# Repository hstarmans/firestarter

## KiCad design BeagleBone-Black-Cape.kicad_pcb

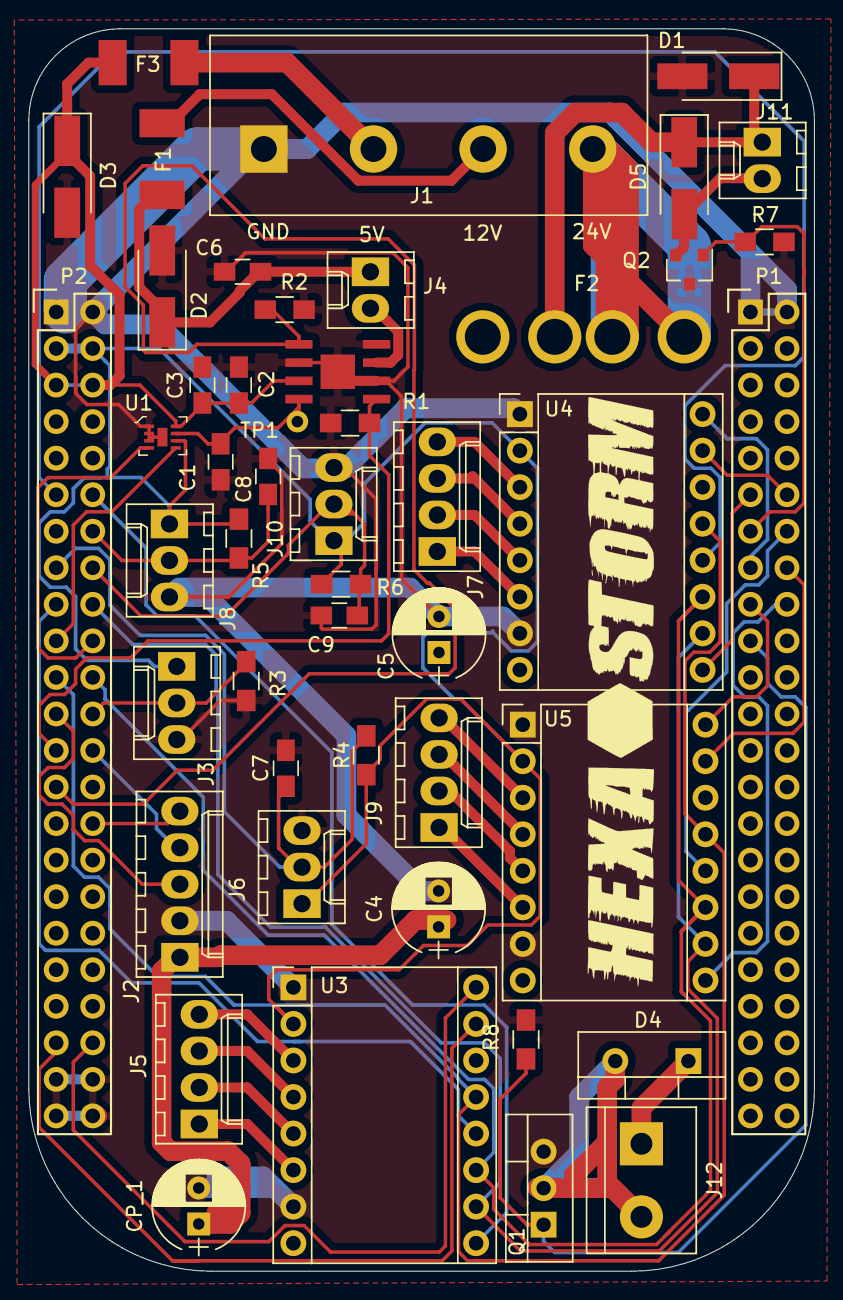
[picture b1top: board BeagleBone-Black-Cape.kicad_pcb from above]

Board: 2 copper layers, 54.6 x 86.4 mm, 49 parts (0 on the bottom side), 52 nets.

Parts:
C1: 47nF; C_0805_HandSoldering
C2, C6: 1uF; C_0805_HandSoldering
C3, C7, C8, C9: 0.1uF; C_0805_HandSoldering
C4, C5: 100uF; CP_Radial_D6.3mm_P2.50mm
CP_1: 100uF; CP_Radial_D6.3mm_P2.50mm
D1, D2, D3, D5: 50V_1A; D_SMA_Handsoldering
D4: STPS1545D; TO-220-2_Vertical
F1: 2A; littlefuse_448
F2: 30A; MCCQ-121
F3: 4A; littlefuse_448
G1: hexastorm
J1: MC000052
J2: MOLEX_2051; Molex_KK-6410-05_05x2.54mm_Straight
J3, J6, J8, J10: MOLEX_2031; Molex_KK-6410-03_03x2.54mm_Straight
J4, J11: MOLEX_2021; Molex_KK-6410-02_02x2.54mm_Straight
J5, J7, J9: MOLEX_2041; Molex_KK-6410-04_04x2.54mm_Straight
J12: EBV-02-D; TerminalBlock_bornier-2_P5.08mm
P1, P2: BeagleBone_Black_Header; Socket_BeagleBone_Black
Q1: IRLB8721PBF; TO-220-3_Vertical
Q2: IRFML8244; SOT-23
R1, R2, R4, R5, R6, R7, R8: 10K; R_0805_HandSoldering
R3: 340K; R_0805_HandSoldering
TP1: TestPoint; Measurement_Point_Round-TH_Small
U1: DIGIPOT_50K; TDFN-8-1EP
U2: U_IC-HKB; ICHKB
U3: X_STEPPER; TMC2130
U4: Y_STEPPER; TMC2130
U5: Z_STEPPER; TMC2130

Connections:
+3V3: J3.1, J6.1, J8.1, J10.1, P2.3, P2.4, R4.1, R5.1, R6.1, U1.6, U3.10, U4.10, U5.10
+5V: C2.2, C3.2, D3.1, F3.1, P2.5, P2.6, U1.8, U2.7
+12V: C6.1, D2.1, F1.1, J4.1
+24V: C4.1, C5.1, CP_1.1, D1.1, D4.1, D5.1, F2.3, F2.4, J2.1, J11.1, J12.1, U3.16, U4.16, U5.16
FAN_PWM: P1.13, Q2.1, R7.2
GND: C1.1, C2.1, C3.1, C4.2, C5.2, C6.2, C7.2, C8.2, C9.2, CP_1.2, D1.2, D2.2, D3.2, J1.1, J2.2, J3.3, J6.3, J8.3, J10.3, P1.1, P1.2, P2.1, P2.2, P2.43, P2.44, P2.45, P2.46, Q1.3, Q2.3, R1.2, R2.1, R3.1, R7.1, R8.1, U1.1, U1.2, U1.3, U1.9, U2.2, U2.4, U2.6, U2.9, U3.9, U3.15, U4.9, U4.15, U5.9, U5.15
IC_HB_PWM1: P2.25, R1.1, U2.1
IC_HB_PWM2: P2.27, R2.2, U2.5
LDK: J4.2, U2.3
unnamed: D4.2, J12.2, Q1.2
unnamed: D5.2, J11.2, Q2.2
unnamed: F1.2, J1.3
unnamed: F2.1, F2.2, J1.4
unnamed: F3.2, J1.2
PH_DIODE: J3.2, P2.24, R3.2
POLY_EN: J2.3, P2.23
POLY_PWM: J2.5, P2.30
POLY_READY: J2.4, P2.26
POT_SCL: P2.19, U1.5
POT_SDA: P2.20, U1.4
POT_W: C1.2, TP1.1, U1.7, U2.8
SPI0_CSX: P2.17, U3.4
SPINDLE_PWM: P1.19, Q1.1, R8.2
SPIO_CSY: P2.11, U4.4
SPIO_CSZ: P1.14, U5.4
SPIO_DI: P2.18, U3.2, U4.2, U5.2
SPIO_DO: P2.21, U3.5, U4.5, U5.5
SPIO_SCL: P2.22, U3.3, U4.3, U5.3
X_1A: J5.3, U3.12
X_1B: J5.4, U3.11
X_2A: J5.2, U3.13
X_2B: J5.1, U3.14
X_DIR: P2.42, U3.8
X_ENABLE: P2.12, U3.1
X_PO: C7.1, J6.2, P2.15, R4.2
X_STEP: P2.41, U3.7
Y_1A: J7.3, U4.12
Y_1B: J7.4, U4.11
Y_2A: J7.2, U4.13
Y_2B: J7.1, U4.14
Y_DIR: P1.15, U4.8
Y_ENABLE: P1.11, U4.1
Y_PO: C8.1, J8.2, P2.14, R5.2
Y_STEP: P1.12, U4.7
Z_1A: J9.3, U5.12
Z_1B: J9.4, U5.11
Z_2A: J9.2, U5.13
Z_2B: J9.1, U5.14
Z_DIR: P1.17, U5.8
Z_ENABLE: P1.18, U5.1
Z_PO: C9.1, J10.2, P2.16, R6.2
Z_STEP: P1.16, U5.7

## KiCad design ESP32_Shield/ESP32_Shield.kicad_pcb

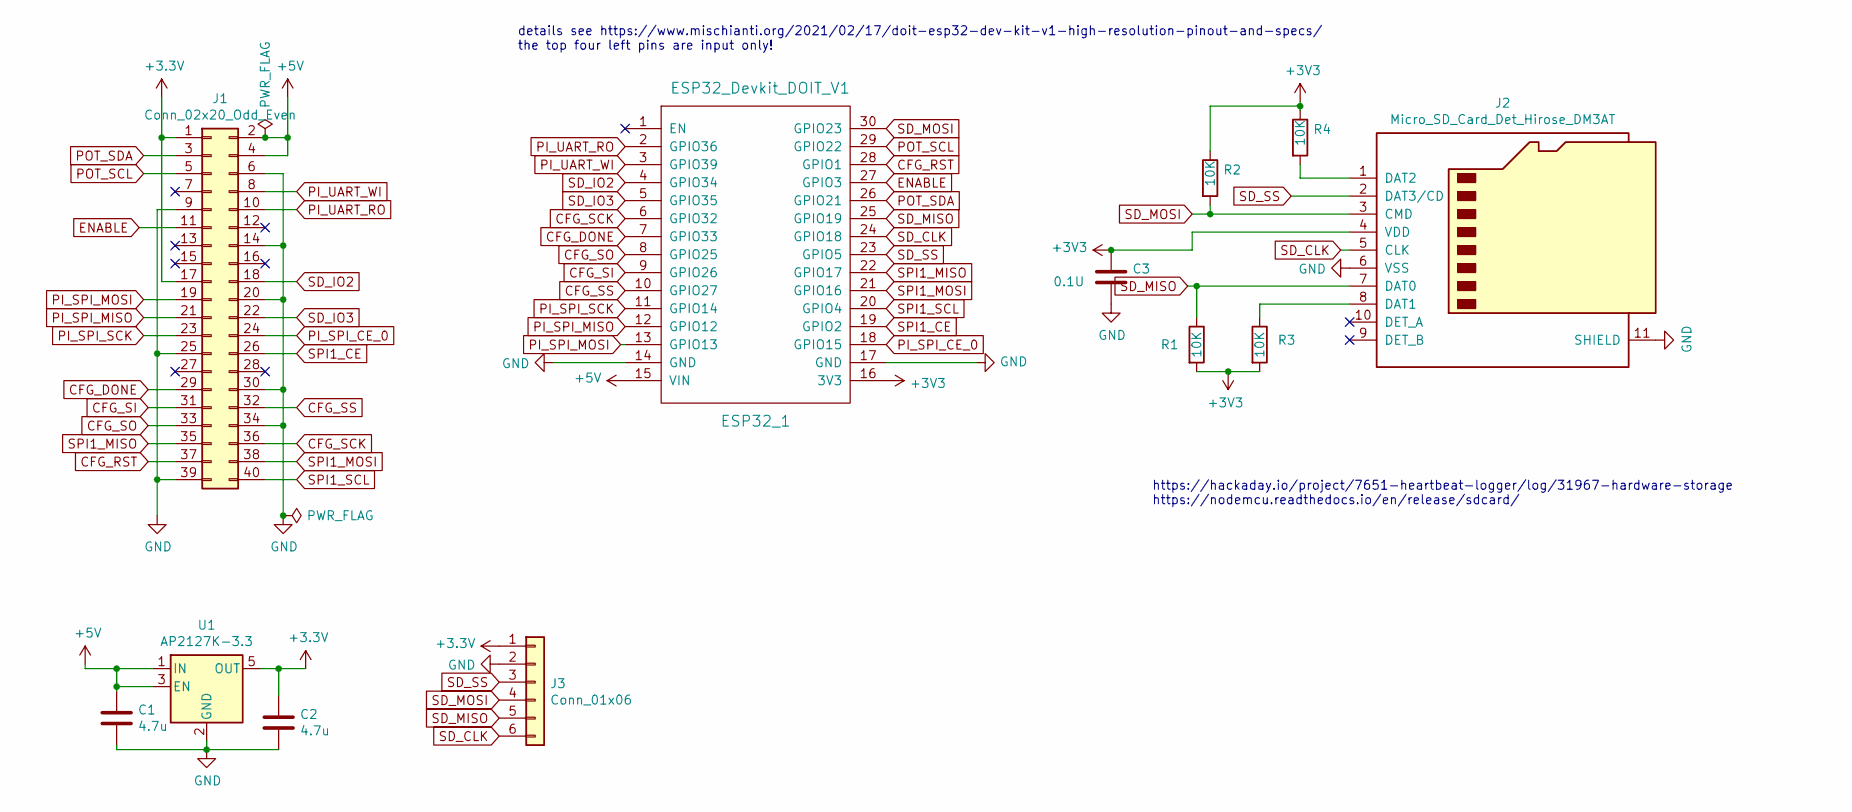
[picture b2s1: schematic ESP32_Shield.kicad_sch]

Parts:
C1, C2: 4.7u; C_0805_2012Metric_Pad1.18x1.45mm_HandSolder
C3: 0.1U; C_0805_2012Metric_Pad1.18x1.45mm_HandSolder
ESP32_1: ESP32_Devkit_DOIT_V1
J1: Conn_02x20_Odd_Even; PinHeader_2x20_P2.54mm_Vertical
J2: Micro_SD_Card_Det_Hirose_DM3AT; microSD_HC_Hirose_DM3AT-SF-PEJM5
J3: Conn_01x06; PinHeader_1x06_P2.54mm_Vertical
R1, R2, R3, R4: 10K; R_0805_2012Metric
U1: AP2127K-3.3; SOT-23-5

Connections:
+5V: C1.1, ESP32_1.15 (VIN), J1.2, J1.4, U1.1 (IN), U1.3 (EN)
CFG_DONE: ESP32_1.7 (GPIO33), J1.29
CFG_RST: ESP32_1.28 (GPIO1), J1.37
CFG_SCK: ESP32_1.6 (GPIO32), J1.36
CFG_SI: ESP32_1.9 (GPIO26), J1.31
CFG_SO: ESP32_1.8 (GPIO25), J1.33
CFG_SS: ESP32_1.10 (GPIO27), J1.32
ENABLE: ESP32_1.27 (GPIO3), J1.11
GND: C1.2, C2.2, C3.2, ESP32_1.14 (GND), ESP32_1.17 (GND), J1.6, J1.9, J1.14, J1.20, J1.25, J1.30, J1.34, J1.39, J2.6 (VSS), J2.11 (SHIELD), J3.2, U1.2 (GND)
unnamed: J2.1 (DAT2), R4.2
unnamed: J2.8 (DAT1), R3.1
PI_SPI_CE_0: ESP32_1.18 (GPIO15), J1.24
PI_SPI_MISO: ESP32_1.12 (GPIO12), J1.21
PI_SPI_MOSI: ESP32_1.13 (GPIO13), J1.19
PI_SPI_SCK: ESP32_1.11 (GPIO14), J1.23
PI_UART_RO: ESP32_1.2 (GPIO36), J1.10
PI_UART_WI: ESP32_1.3 (GPIO39), J1.8
POT_SCL: ESP32_1.29 (GPIO22), J1.5
POT_SDA: ESP32_1.26 (GPIO21), J1.3
SD_CLK: ESP32_1.24 (GPIO18), J2.5 (CLK), J3.6
SD_IO2: ESP32_1.4 (GPIO34), J1.18
SD_IO3: ESP32_1.5 (GPIO35), J1.22
SD_MISO: ESP32_1.25 (GPIO19), J2.7 (DAT0), J3.5, R1.1
SD_MOSI: ESP32_1.30 (GPIO23), J2.3 (CMD), J3.4, R2.2
SD_SS: ESP32_1.23 (GPIO5), J2.2 (DAT3/CD), J3.3
SPI1_CE: ESP32_1.19 (GPIO2), J1.26
SPI1_MISO: ESP32_1.22 (GPIO17), J1.35
SPI1_MOSI: ESP32_1.21 (GPIO16), J1.38
SPI1_SCL: ESP32_1.20 (GPIO4), J1.40

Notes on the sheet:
details see https://www.mischianti.org/2021/02/17/doit-esp32-dev-kit-v1-high-resolution-pinout-and-specs/ the top four left pins are input only!
https://hackaday.io/project/7651-heartbeat-logger/log/31967-hardware-storage https://nodemcu.readthedocs.io/en/release/sdcard/

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
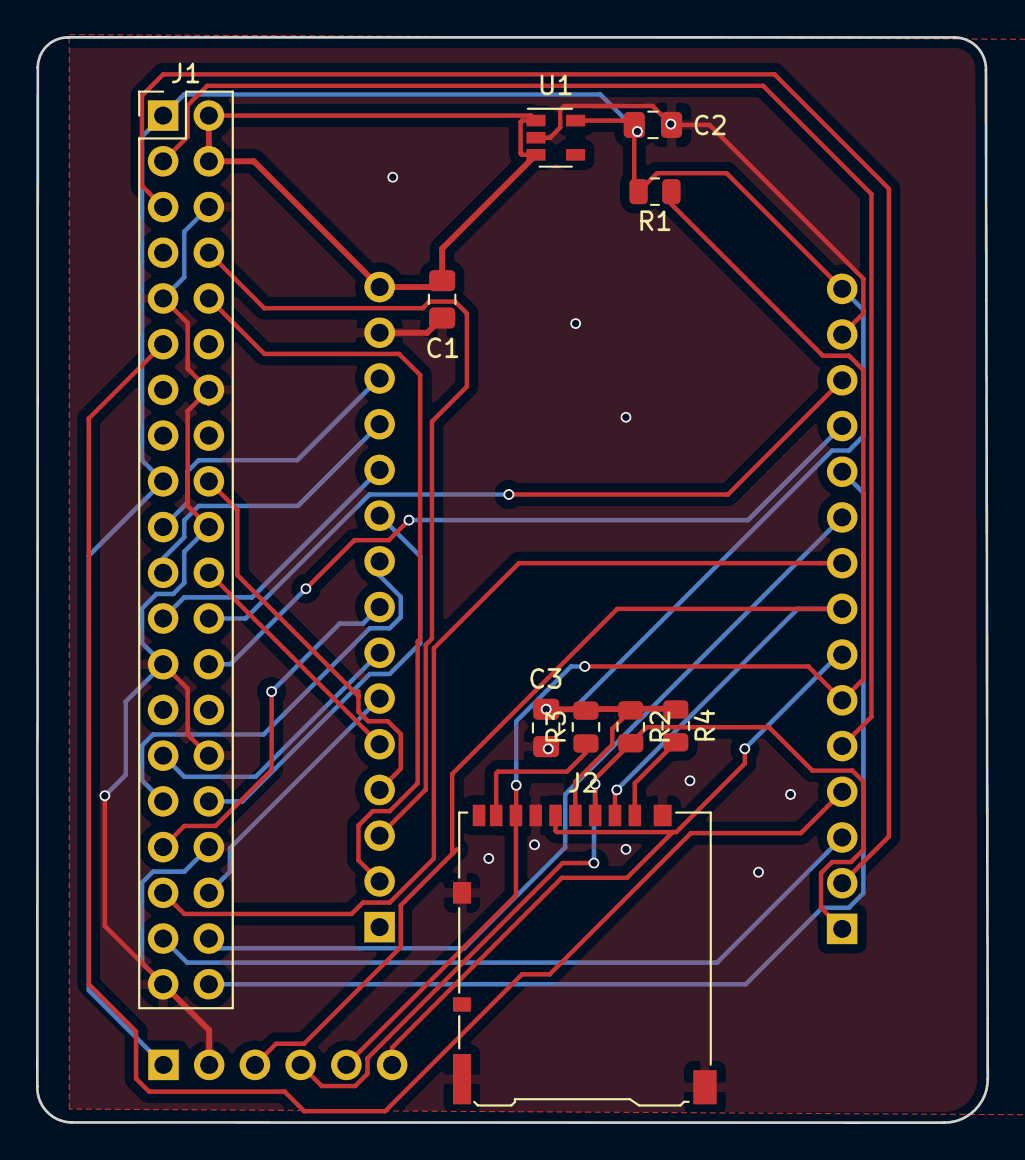
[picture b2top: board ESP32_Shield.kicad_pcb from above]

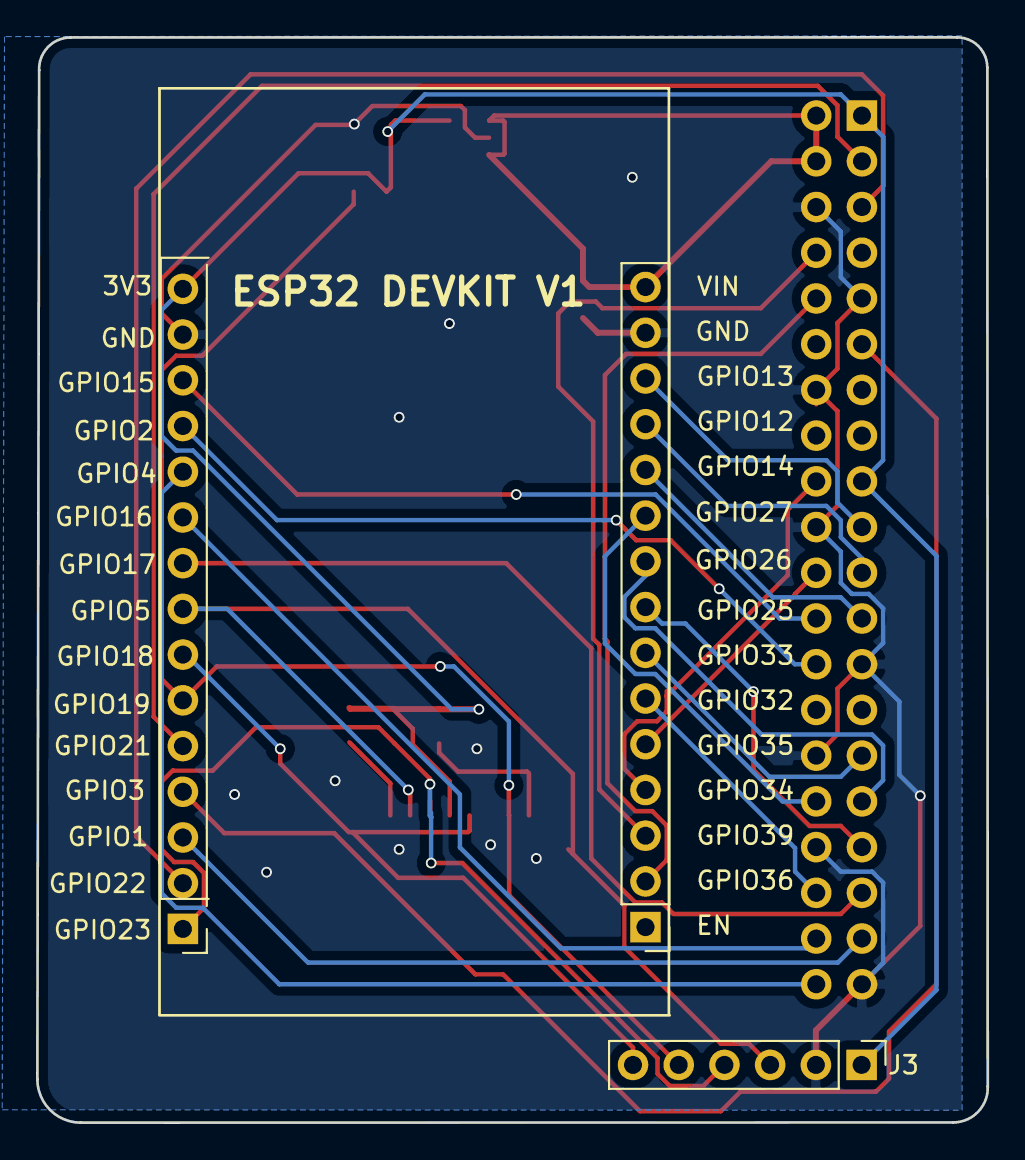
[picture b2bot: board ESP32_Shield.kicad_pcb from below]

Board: 2 copper layers, 52.8 x 60.3 mm, 12 parts (2 on the bottom side), 30 nets.

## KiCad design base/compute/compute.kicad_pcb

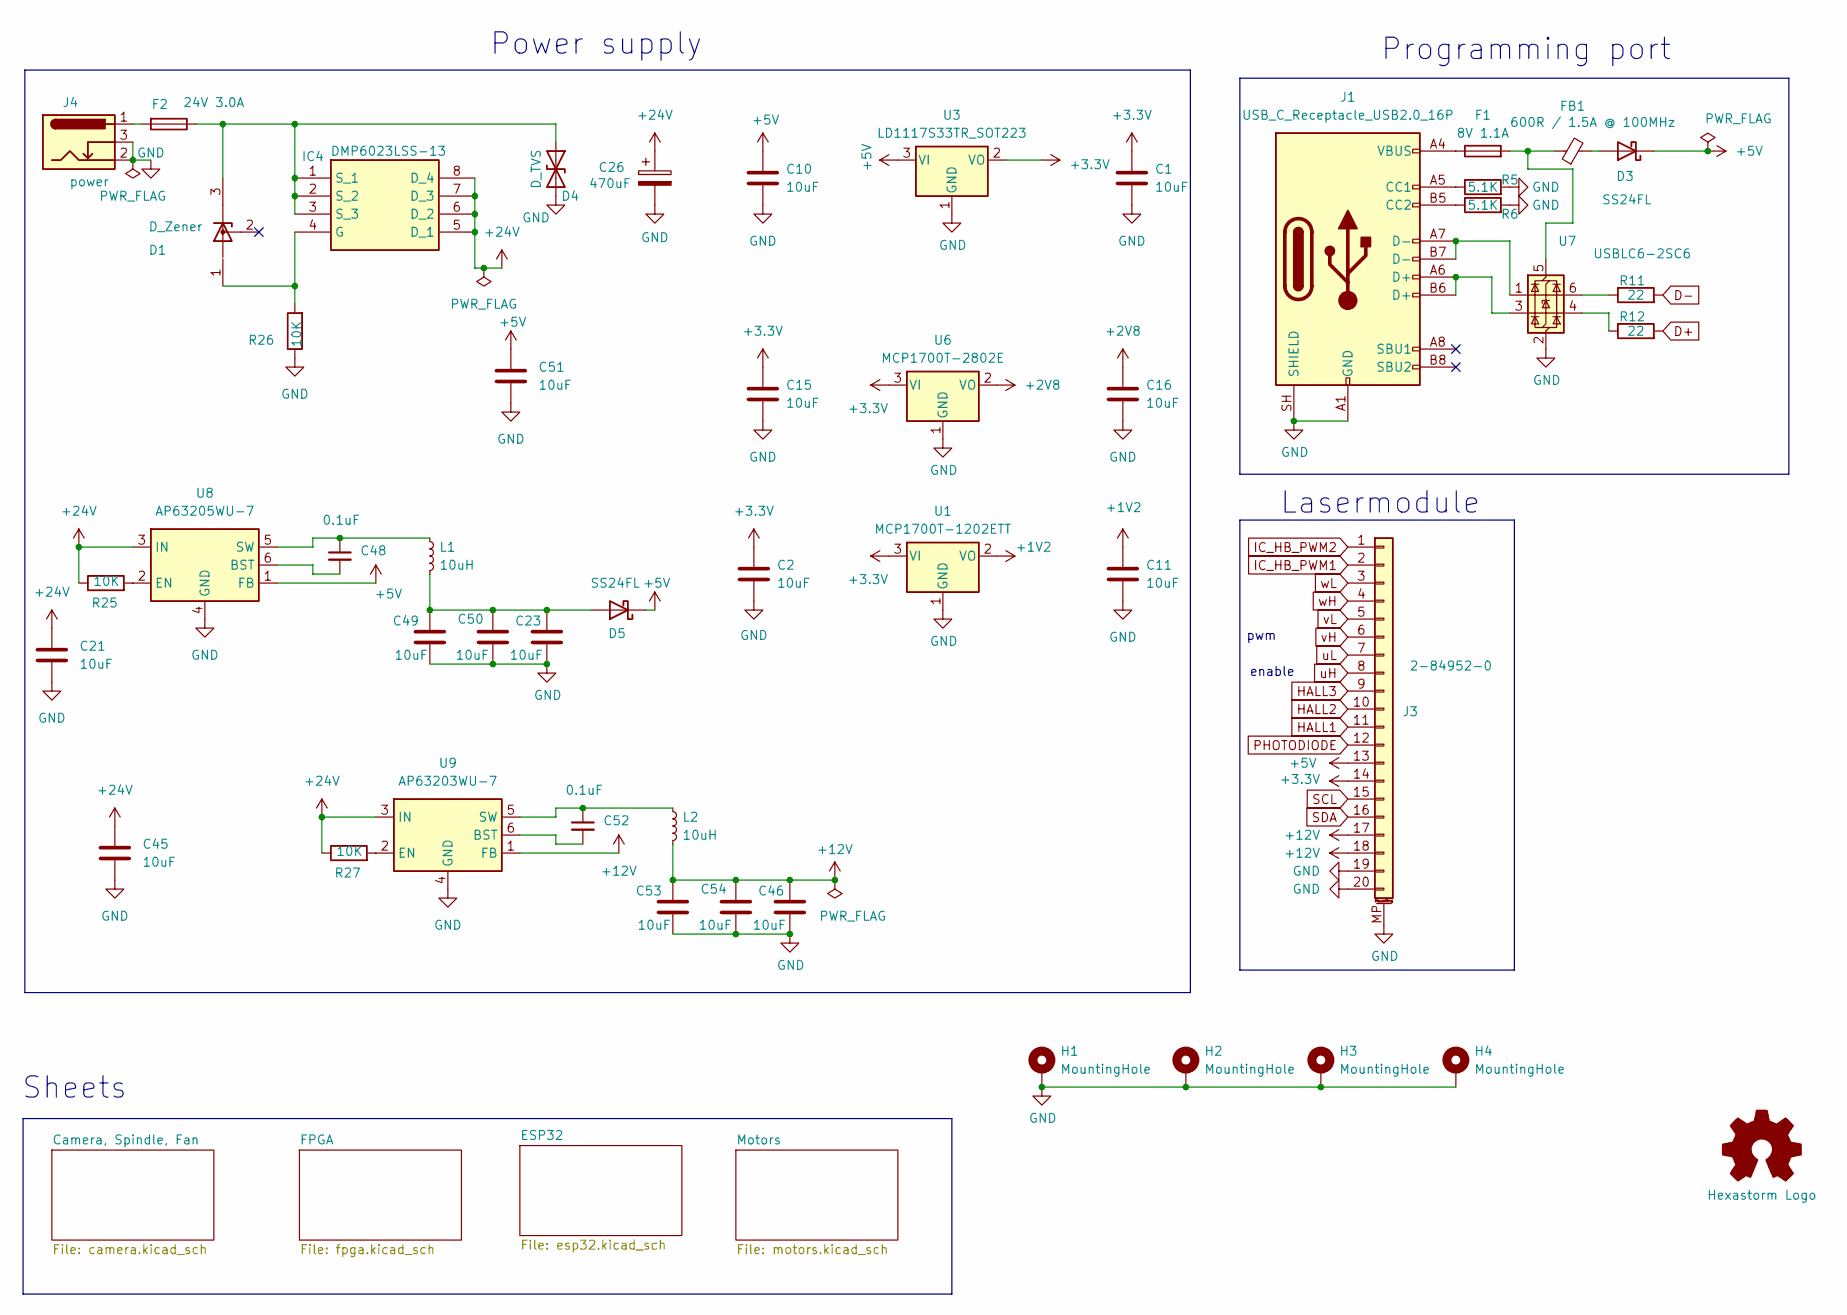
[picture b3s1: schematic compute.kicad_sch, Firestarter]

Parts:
C1, C2, C10, C11, C15, C16, C49, C50, C53, C54: 10uF; C_0805_2012Metric_Pad1.18x1.45mm_HandSolder; mouser# 81-GRM21BR61H106KE3L; farnell# 3790440
C21, C23, C45, C46, C51: 10uF; C_0805_2012Metric_Pad1.18x1.45mm_HandSolder; mouser# 81-GRM21BR61H106KE3L
C26: 470uF; CP_Elec_10x10.5; mouser# 667-EEE-FK1V471SP; farnell# 2507737
C48, C52: 0.1uF; C_0805_2012Metric_Pad1.18x1.45mm_HandSolder; mouser# 80-C0805C104J5R
D1: D_Zener; SOT-23; mouser# 2675184
D3, D5: SS24FL; D_SMA; mouser# 512-SS24FL; farnell# 2822566
D4: D_TVS; D_SMB; mouser# 652-SMBJ13CA; farnell# 2765106
F1: 8V 1.1A; Fuse_1206_3216Metric; mouser# 576-1206L110THYR; farnell# 2383294
F2: 24V 3.0A; Fuse_2920_7451Metric; mouser# 652-MF-LSMF300/24X-2
FB1: 600R / 1.5A @ 100MHz; L_0805_2012Metric; mouser# 81-BLM21PG601SN1D
G1: hexastorm
H1, H2, H3, H4: MountingHole; MountingHole_2.2mm_M2_Pad_Via; mouser# 710-970050244
IC4: DMP6023LSS-13; SOIC-8_3.9x4.9mm_P1.27mm; Manufacturer_Part_Number DMP6023LSS-13; Mouser Part Number 621-DMP6023LSS-13
J1: USB_C_Receptacle_USB2.0_16P; USB_C_Receptacle_GCT_USB4105-xx-A_16P_TopMnt_Horizontal; mouser# 640-USB4105-GF-A
J3: 2-84952-0; mouser# 571-2-84952-0
J4: power; BarrelJack_CUI_PJ-036AH-SMT_Horizontal; mouser# 490-PJ-036AH-SMT-TR
L1, L2: 10uH; L_Bourns_SRP5030T; mouser# 652-SRP5030T-100M
R5, R6: 5.1K; R_0805_2012Metric; mouser# 71-CRCW0805-5.1K-E3; farnell# 1469937
R11, R12: 22; R_0805_2012Metric; mouser# 71-CRCW0805-22-E3; farnell# 1652962
R25, R26, R27: 10K; R_0805_2012Metric; mouser# 71-CRCW080510K0JNEAC; farnell# 2826162
U1: MCP1700T-1202ETT; SOT-23; mouser# 579-MCP1700T1202E/TT
U3: LD1117S33TR_SOT223; SOT-23; mouser# 511-LD1117S33C; farnell# 1467779
U6: MCP1700T-2802E; SOT-23; mouser# 579-MCP1700T-2802ETT
U7: USBLC6-2SC6; SOT-23-6; mouser# 511-USBLC6-2SC6; farnell# 1269406
U8: AP63205WU-7; TSOT-23-6; mouser# 621-AP63205WU-7; farnell# 3518308
U9: AP63203WU-7; TSOT-23-6; mouser# 621-AP63203WU-7; farnell# 3518307

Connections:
+1V2: C11.1, U1.2 (VO); also elsewhere on the board
+2V8: C16.1, U6.2 (VO); also elsewhere on the board
+3.3V: C1.1, C2.1, C15.1, J3.14, U1.3 (VI), U3.2 (VO), U6.3 (VI); also elsewhere on the board
+5V: C10.1, C51.1, D3.1 (K), D5.1 (K), J3.13, U3.3 (VI), U8.1 (FB)
+12V: C46.1, C53.1, C54.1, J3.17, J3.18, L2.2, U9.1 (FB); also elsewhere on the board
+24V: C21.1, C26.1, C45.1, IC4.5 (D_1), IC4.6 (D_2), IC4.7 (D_3), IC4.8 (D_4), R25.1, R27.1, U8.3 (IN), U9.3 (IN); also elsewhere on the board
D+: R12.2; also elsewhere on the board
D-: R11.2; also elsewhere on the board
GND: C1.2, C2.2, C10.2, C11.2, C15.2, C16.2, C21.2, C23.2, C26.2, C45.2, C46.2, C49.2, C50.2, C51.2, C53.2, C54.2, D4.2 (A2), H1.1 (1_1), H2.1 (1_1), H3.1 (1_1), H4.1 (1_1), J1.A1 (GND), J1.A12 (GND), J1.B1 (GND), J1.B12 (GND), J1.SH (SHIELD), J3.19, J3.20, J3.MP (MountPin), J4.2, J4.3, R5.2, R6.2, R26.1, U1.1 (GND), U3.1 (GND), U6.1 (GND), U7.2 (GND), U8.4 (GND), U9.4 (GND); also elsewhere on the board
HALL1: J3.11; also elsewhere on the board
HALL2: J3.10; also elsewhere on the board
HALL3: J3.9; also elsewhere on the board
IC_HB_PWM1: J3.2; also elsewhere on the board
IC_HB_PWM2: J3.1; also elsewhere on the board
unnamed: D3.2 (A), FB1.2
unnamed: D1.3 (K), D4.1 (A1), F2.1, IC4.1 (S_1), IC4.2 (S_2), IC4.3 (S_3)
unnamed: C23.1, C49.1, C50.1, D5.2 (A), L1.2
unnamed: F1.1, J1.A4 (VBUS), J1.A9 (VBUS), J1.B4 (VBUS), J1.B9 (VBUS)
unnamed: F2.2, J4.1
unnamed: D1.1 (K), IC4.4 (G), R26.2
unnamed: J1.A5 (CC1), R5.1
unnamed: J1.B5 (CC2), R6.1
unnamed: J1.A6 (D+), J1.B6 (D+), U7.3 (I/O2)
unnamed: J1.A7 (D-), J1.B7 (D-), U7.1 (I/O1)
unnamed: R11.1, U7.6 (I/O1)
unnamed: R12.1, U7.4 (I/O2)
unnamed: F1.2, FB1.1, U7.5 (VBUS)
unnamed: C48.2, U8.6 (BST)
unnamed: R25.2, U8.2 (EN)
unnamed: C48.1, L1.1, U8.5 (SW)
unnamed: C52.2, U9.6 (BST)
unnamed: R27.2, U9.2 (EN)
unnamed: C52.1, L2.1, U9.5 (SW)
PHOTODIODE: J3.12; also elsewhere on the board
SCL: J3.15; also elsewhere on the board
SDA: J3.16; also elsewhere on the board
uH: J3.8; also elsewhere on the board
uL: J3.7; also elsewhere on the board
vH: J3.6; also elsewhere on the board
vL: J3.5; also elsewhere on the board
wH: J3.4; also elsewhere on the board
wL: J3.3; also elsewhere on the board

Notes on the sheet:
pwm
Programming port
Sheets
Power supply
enable
Lasermodule

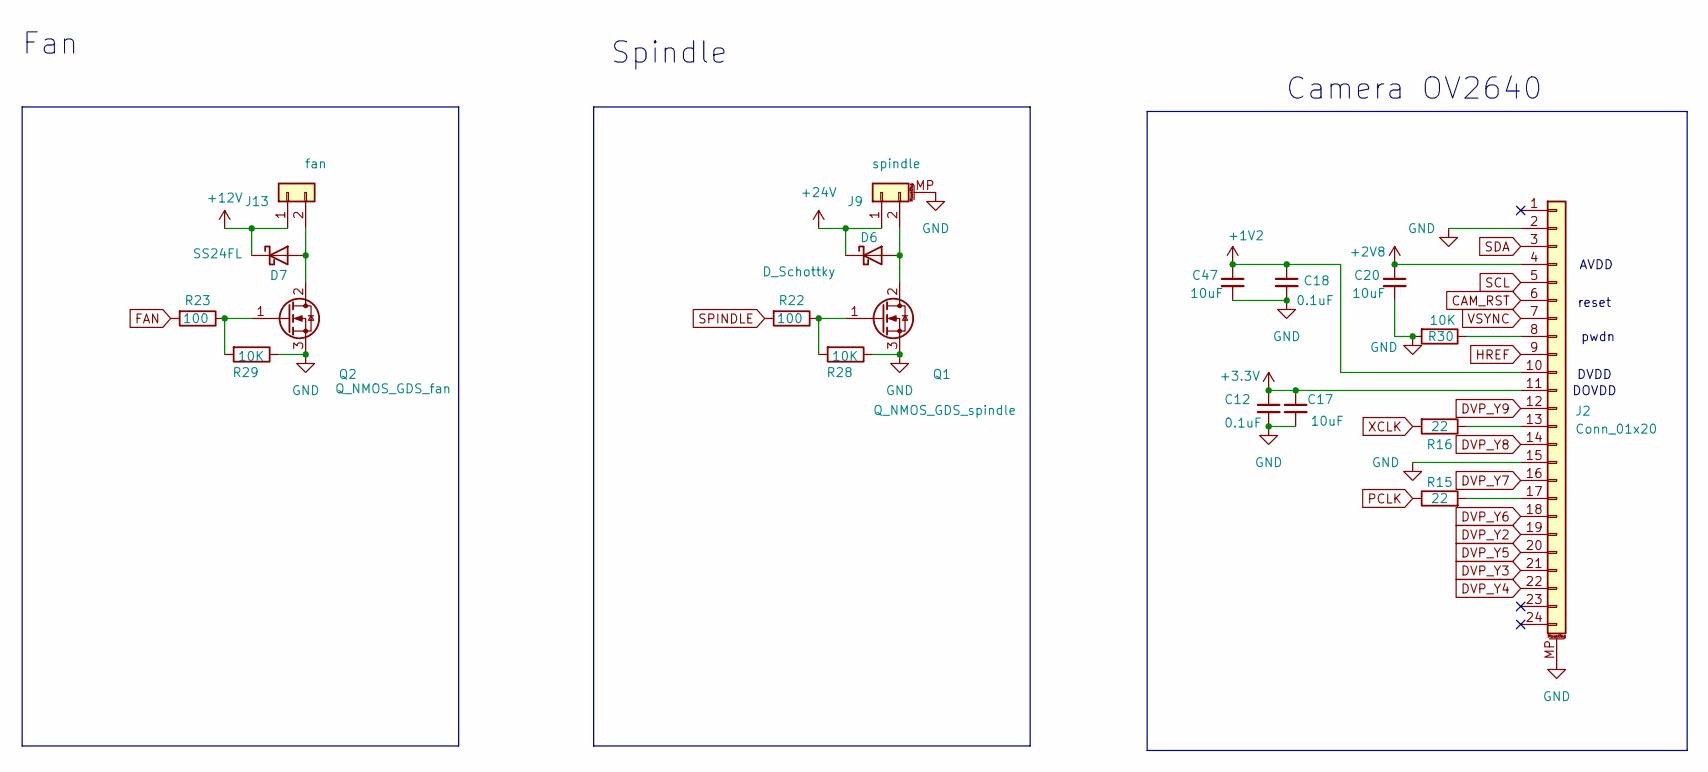
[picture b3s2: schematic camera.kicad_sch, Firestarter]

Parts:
C12, C18: 0.1uF; C_0805_2012Metric_Pad1.18x1.45mm_HandSolder; mouser# 80-C0805C104J5R
C17, C20, C47: 10uF; C_0805_2012Metric_Pad1.18x1.45mm_HandSolder; mouser# 81-GRM21BR61H106KE3L; farnell# 3790440
D6: D_Schottky; D_SMA; mouser# 750-SS56-HF
D7: SS24FL; D_SMA; mouser# 512-SS24FL; farnell# 2822566
J2: Conn_01x20; Hirose_FH12-24S-0.5SH_1x24-1MP_P0.50mm_Horizontal; mouser# 798-FH12-24S-0.5SH55; farnell# 1324552
J9: spindle; 21548291; mouser# 571-2154829-1
J13: fan; TSM-102-01-L-SV; mouser# 200-TSM10201TSV
Q1: Q_NMOS_GDS_spindle; TO-252-2; mouser# 511-STD120N4LF6
Q2: Q_NMOS_GDS_fan; SOT-23; mouser# 512-2N7002
R15, R16: 22; R_0805_2012Metric; mouser# 71-CRCW0805-22-E3; farnell# 1652962
R22, R23: 100; R_0805_2012Metric_Pad1.20x1.40mm_HandSolder; mouser# 71-CRCW0805-100
R28, R29, R30: 10K; R_0805_2012Metric; mouser# 71-CRCW080510K0JNEAC; farnell# 2826162

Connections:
+1V2: C18.1, C47.1, J2.10; also elsewhere on the board
+2V8: C20.1, J2.4; also elsewhere on the board
+3.3V: C12.1, C17.1, J2.11; also elsewhere on the board
+12V: D7.1 (K), J13.1; also elsewhere on the board
+24V: D6.1 (K), J9.1; also elsewhere on the board
CAM_RST: J2.6; also elsewhere on the board
DVP_Y2: J2.19; also elsewhere on the board
DVP_Y3: J2.21; also elsewhere on the board
DVP_Y4: J2.22; also elsewhere on the board
DVP_Y5: J2.20; also elsewhere on the board
DVP_Y6: J2.18; also elsewhere on the board
DVP_Y7: J2.16; also elsewhere on the board
DVP_Y8: J2.14; also elsewhere on the board
DVP_Y9: J2.12; also elsewhere on the board
FAN: R23.2; also elsewhere on the board
GND: C12.2, C17.2, C18.2, C20.2, C47.2, J2.2, J2.15, J2.MP (MountPin), J9.MP (MountPin), Q1.3 (S), Q2.3 (S), R28.1, R29.1, R30.2; also elsewhere on the board
HREF: J2.9; also elsewhere on the board
unnamed: D6.2 (A), J9.2, Q1.2 (D)
unnamed: D7.2 (A), J13.2, Q2.2 (D)
unnamed: J2.8, R30.1
unnamed: J2.13, R16.1
unnamed: J2.17, R15.2
unnamed: Q1.1 (G), R22.1, R28.2
unnamed: Q2.1 (G), R23.1, R29.2
PCLK: R15.1; also elsewhere on the board
SCL: J2.5; also elsewhere on the board
SDA: J2.3; also elsewhere on the board
SPINDLE: R22.2; also elsewhere on the board
VSYNC: J2.7; also elsewhere on the board
XCLK: R16.2; also elsewhere on the board

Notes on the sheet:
DOVDD
DVDD
Spindle
pwdn
reset
Fan
Camera OV2640
AVDD

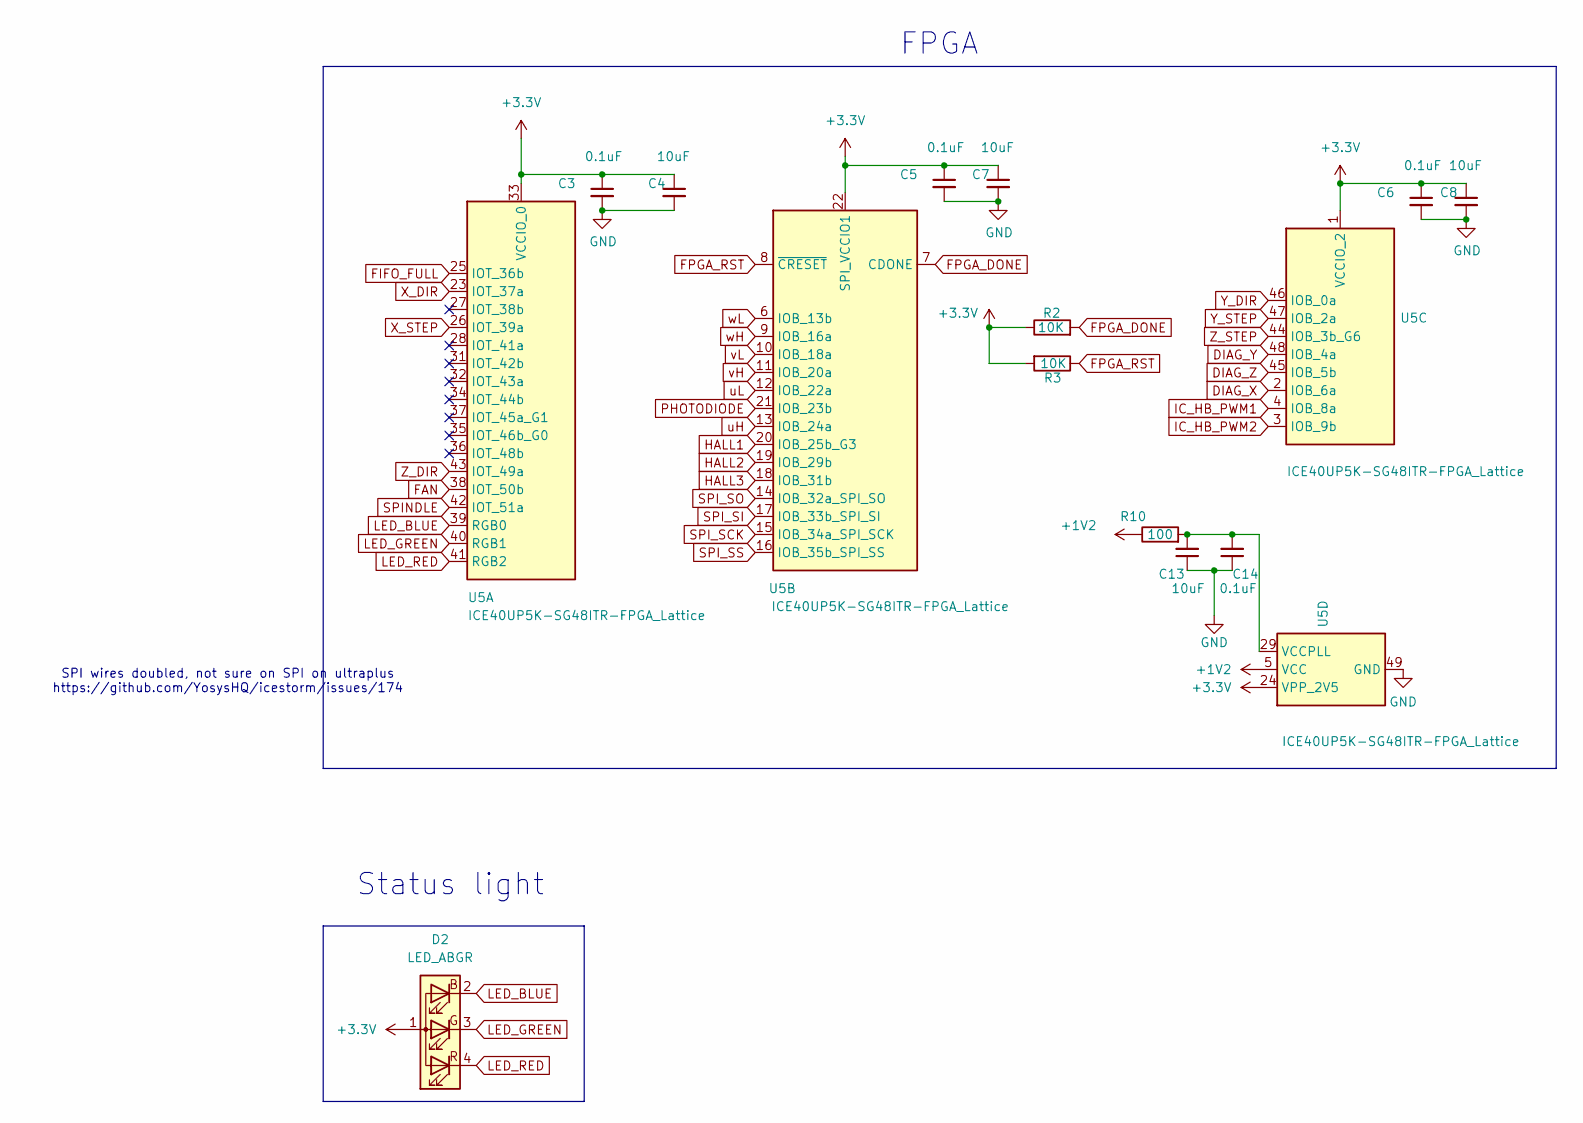
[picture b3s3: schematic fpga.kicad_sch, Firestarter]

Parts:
C3, C5, C6, C14: 0.1uF; C_0805_2012Metric_Pad1.18x1.45mm_HandSolder; mouser# 80-C0805C104J5R
C4, C7, C8, C13: 10uF; C_0805_2012Metric_Pad1.18x1.45mm_HandSolder; mouser# 81-GRM21BR61H106KE3L; farnell# 3790440
D2: LED_ABGR; LED_Cree-PLCC4_2x2mm_CW; mouser# 941-CLMVCFKACL1D1L71; farnell# 3625420
R2, R3: 10K; R_0805_2012Metric; mouser# 71-CRCW080510K0JNEAC; farnell# 2826162
R10: 100; R_0805_2012Metric_Pad1.20x1.40mm_HandSolder; mouser# 71-CRCW0805-100
U5: ICE40UP5K-SG48ITR-FPGA_Lattice; QFN-48-1EP_7x7mm_P0.5mm_EP5.6x5.6mm; mouser# 842-ICE40UP5K-SG48I

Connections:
+1V2: R10.1, U5.5 (VCC), U5.30 (VCC); also elsewhere on the board
+3.3V: C3.1, C4.1, C5.1, C6.1, C7.1, C8.1, D2.1 (A), R2.1, R3.2, U5.1 (VCCIO_2), U5.22 (SPI_VCCIO1), U5.24 (VPP_2V5), U5.33 (VCCIO_0); also elsewhere on the board
DIAG_X: U5.2 (IOB_6a); also elsewhere on the board
DIAG_Y: U5.48 (IOB_4a); also elsewhere on the board
DIAG_Z: U5.45 (IOB_5b); also elsewhere on the board
FAN: U5.38 (IOT_50b); also elsewhere on the board
FIFO_FULL: U5.25 (IOT_36b); also elsewhere on the board
FPGA_DONE: R2.2, U5.7 (CDONE); also elsewhere on the board
FPGA_RST: R3.1, U5.8 (~CRESET); also elsewhere on the board
GND: C3.2, C4.2, C5.2, C6.2, C7.2, C8.2, C13.1, C14.1, U5.49 (GND); also elsewhere on the board
HALL1: U5.20 (IOB_25b_G3); also elsewhere on the board
HALL2: U5.19 (IOB_29b); also elsewhere on the board
HALL3: U5.18 (IOB_31b); also elsewhere on the board
IC_HB_PWM1: U5.4 (IOB_8a); also elsewhere on the board
IC_HB_PWM2: U5.3 (IOB_9b); also elsewhere on the board
LED_BLUE: D2.2 (BK), U5.39 (RGB0)
LED_GREEN: D2.3 (GK), U5.40 (RGB1)
LED_RED: D2.4 (RK), U5.41 (RGB2)
unnamed: C13.2, C14.2, R10.2, U5.29 (VCCPLL)
PHOTODIODE: U5.21 (IOB_23b); also elsewhere on the board
SPINDLE: U5.42 (IOT_51a); also elsewhere on the board
SPI_SCK: U5.15 (IOB_34a_SPI_SCK); also elsewhere on the board
SPI_SI: U5.17 (IOB_33b_SPI_SI); also elsewhere on the board
SPI_SO: U5.14 (IOB_32a_SPI_SO); also elsewhere on the board
SPI_SS: U5.16 (IOB_35b_SPI_SS); also elsewhere on the board
X_DIR: U5.23 (IOT_37a); also elsewhere on the board
X_STEP: U5.26 (IOT_39a); also elsewhere on the board
Y_DIR: U5.46 (IOB_0a); also elsewhere on the board
Y_STEP: U5.47 (IOB_2a); also elsewhere on the board
Z_DIR: U5.43 (IOT_49a); also elsewhere on the board
Z_STEP: U5.44 (IOB_3b_G6); also elsewhere on the board
uH: U5.13 (IOB_24a); also elsewhere on the board
uL: U5.12 (IOB_22a); also elsewhere on the board
vH: U5.11 (IOB_20a); also elsewhere on the board
vL: U5.10 (IOB_18a); also elsewhere on the board
wH: U5.9 (IOB_16a); also elsewhere on the board
wL: U5.6 (IOB_13b); also elsewhere on the board

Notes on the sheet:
FPGA
SPI wires doubled, not sure on SPI on ultraplus https://github.com/YosysHQ/icestorm/issues/174
Status light
